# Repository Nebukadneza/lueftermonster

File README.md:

# Lüftermonster

## TL;DR:
You want to control up to 15 PC Fans by PWM, read the RPM of every single one, attach up to 4 DS18b20 Temperature Probes, and have all this exposed by API, Web-interface or into Home-Assistant? This is for you!

## Description
Many water based central heating systems that use radiators benefit from a reduced system temperature. Whether it´s fuel-value gas or oil, or a heat-pump, reducing the systems primary temperature results in energy savings.

Radiators can only radiate a certain amount of heat defined by their construction and size - unless we force some air through them! This can be done passively by building a "chimney" around them and using the chimney-effect, and/or by attaching fans. Many commercially available fan-retrofitting kits or even radiators with fans included use noisy low quality fans, don´t allow for a lot of control, and are often very expensive. So you might want to add your own.

Lüftermonster is a project that provides you with a hardware PCB and software to control up to 15 PC Fans, allowing you to make them noiseless by PWM. The tacho signals (RPM) of all fans are monitored so you can monitor them and detect broken fans. Furthermore, you can add up to 4 DS18b20 temperature sensors in order to measure water- and air-temperature to finely control your fan-speed depending on your heating and room situation. Lüftermonster is WIFI-enabled by relying on a trusty ESP32.

By implementing Lüftermonster using [ESPHome](https://esphome.io/), we make it maintainable and easily customizable. It integrates seamlessly into [Home-Assistant](https://www.home-assistant.io/) and other home-automation solutions. If you don´t have or want one, you can use the local API or web-based interface to control and monitor your Lüftermonster.

The hardware is designed so that it can be easily and affordably ordered off [JLCPCB](https://jlcpcb.com/) ready-made with components soldered by them!

# Building one
## What you need
- Lüftermonster PCB(s).
- A USB-to-Serial adapter, like the ubiquitous "FTDI" ones. Find them off your local maker store, EBay, AliExpress, Amazon or similar.
- "Dupont" female-to-female cables to connect Lüftermonster to the USB-to-Serial adapter.
- 20x5mm 2A slow fuses.
- Up to 15 PC Fans per Lüftermonster: 12V, 4-pin.
- (Optional: up to 4 DS18b20 temperature probes per Lüftermonster, including 3-pin cables)

## Hardware
### Fabrication
Gerber files and BOM/CPL data compatible with the JLCPCB assembly service can be found in the `fab` directory. This is a 2-layer PCB compatible with their "Economic" class PCBA service.

### Stuffing options

A few stuffing options are available on the PCB. The corresponding 0R resistors use 0603 sizes (compared to the 0402 size used for everything else) to be more convenient to rework with basic equipment. If you don't have KiCad installed, you can use the [Interactive HTML BOM](fab/ibom.html) to locate the components on the board.

* PWM output voltage levels. Exactly one of the following 0R resistors must be populated.
  * R10: 5V (default)
  * R11: 3.3V
  * R13: Equal to supply voltage (i.e. usually 12V)
* 1-wire supply: Exactly one of the following 0R resistors must be populated.
  * R32: 3.3V (default)
  * R12: 5V

## Software
### Preparation
Install ESPHome, please refer to their excellent ["Getting Started" Sections](https://esphome.io/). Note: You only need to get esphome itself running, not write any YAML-Files yourself.

Copy `firmware/secrets.yaml.template` to `firmware/secrets.yaml`, and edit according to your environment.

Open and edit `firmware/lueftermonster.yaml` according to your environment. Note: If you have multiple Lüftermonsters, please assign unique and meaningful names like "lueftermonster-livingroom-left" or similar.

### Programming
Connect the USB-to-Serial adapter to your Lüftermonster, as follows:
  - VCC -> 3v3
  - GND -> GND
  - RX -> TX
  - TX -> RX
  - EN -> CTS
  - IO0 -> DTR

Attach your USB-to-Serial adapter to your computer

Follow the ESPHome Getting-Started guide you´ve chosen to "run" or "upload" `firmware/lueftermonster.yaml`.

Note: `esptool`, which is internally used by ESPHome to program the ESP32 tries to reset the ESP32 and bring it into programming mode. If this does not work, it may be that "Automatic bootloader mode" does not work. Please [refer to the documentation](https://docs.espressif.com/projects/esptool/en/latest/esp32/advanced-topics/boot-mode-selection.html#automatic-bootloader).

### Usage
After a brief period, you should be able to open `http://<the-name-you-set-in-the-yaml>.local/`, for example http://lueftermonster-livingroom-left.local/ .

Now, you can control the fan speed, and check the fans current RPMs. Note: RPM are not updated often, so it make take a while for all of them to display, and for speed changes to become visible. This is intentional since the information is most useful for outage detection, and does not need to be reported often.

To connect to Home-Assistant refer to the [ESPHome documentation](https://esphome.io/guides/getting_started_hassio#connecting-your-device-to-home-assistant)

### Connect a fan
Since the "proper" PC Fan connectors are not cheaply sourcable from JLCPCB (and THT parts incur a hand-soldering fee/delay), we cheaped out by using standard 2.54mm connection pins. This works, but

_**IS NOT SAFE TO CONNECT IN REVERSE!**_

So you need to pay attention to how you connect your fans. Refer to the silk-screen on the right of Lüftermonster for the pinout of the connectors. With the two "latches" of a standard PC Fan connector, it is correct to connect the fan like this:

### Connecting DS18b20 Temperature Sensors
TODO: Section about DS18b20 address finding and such.

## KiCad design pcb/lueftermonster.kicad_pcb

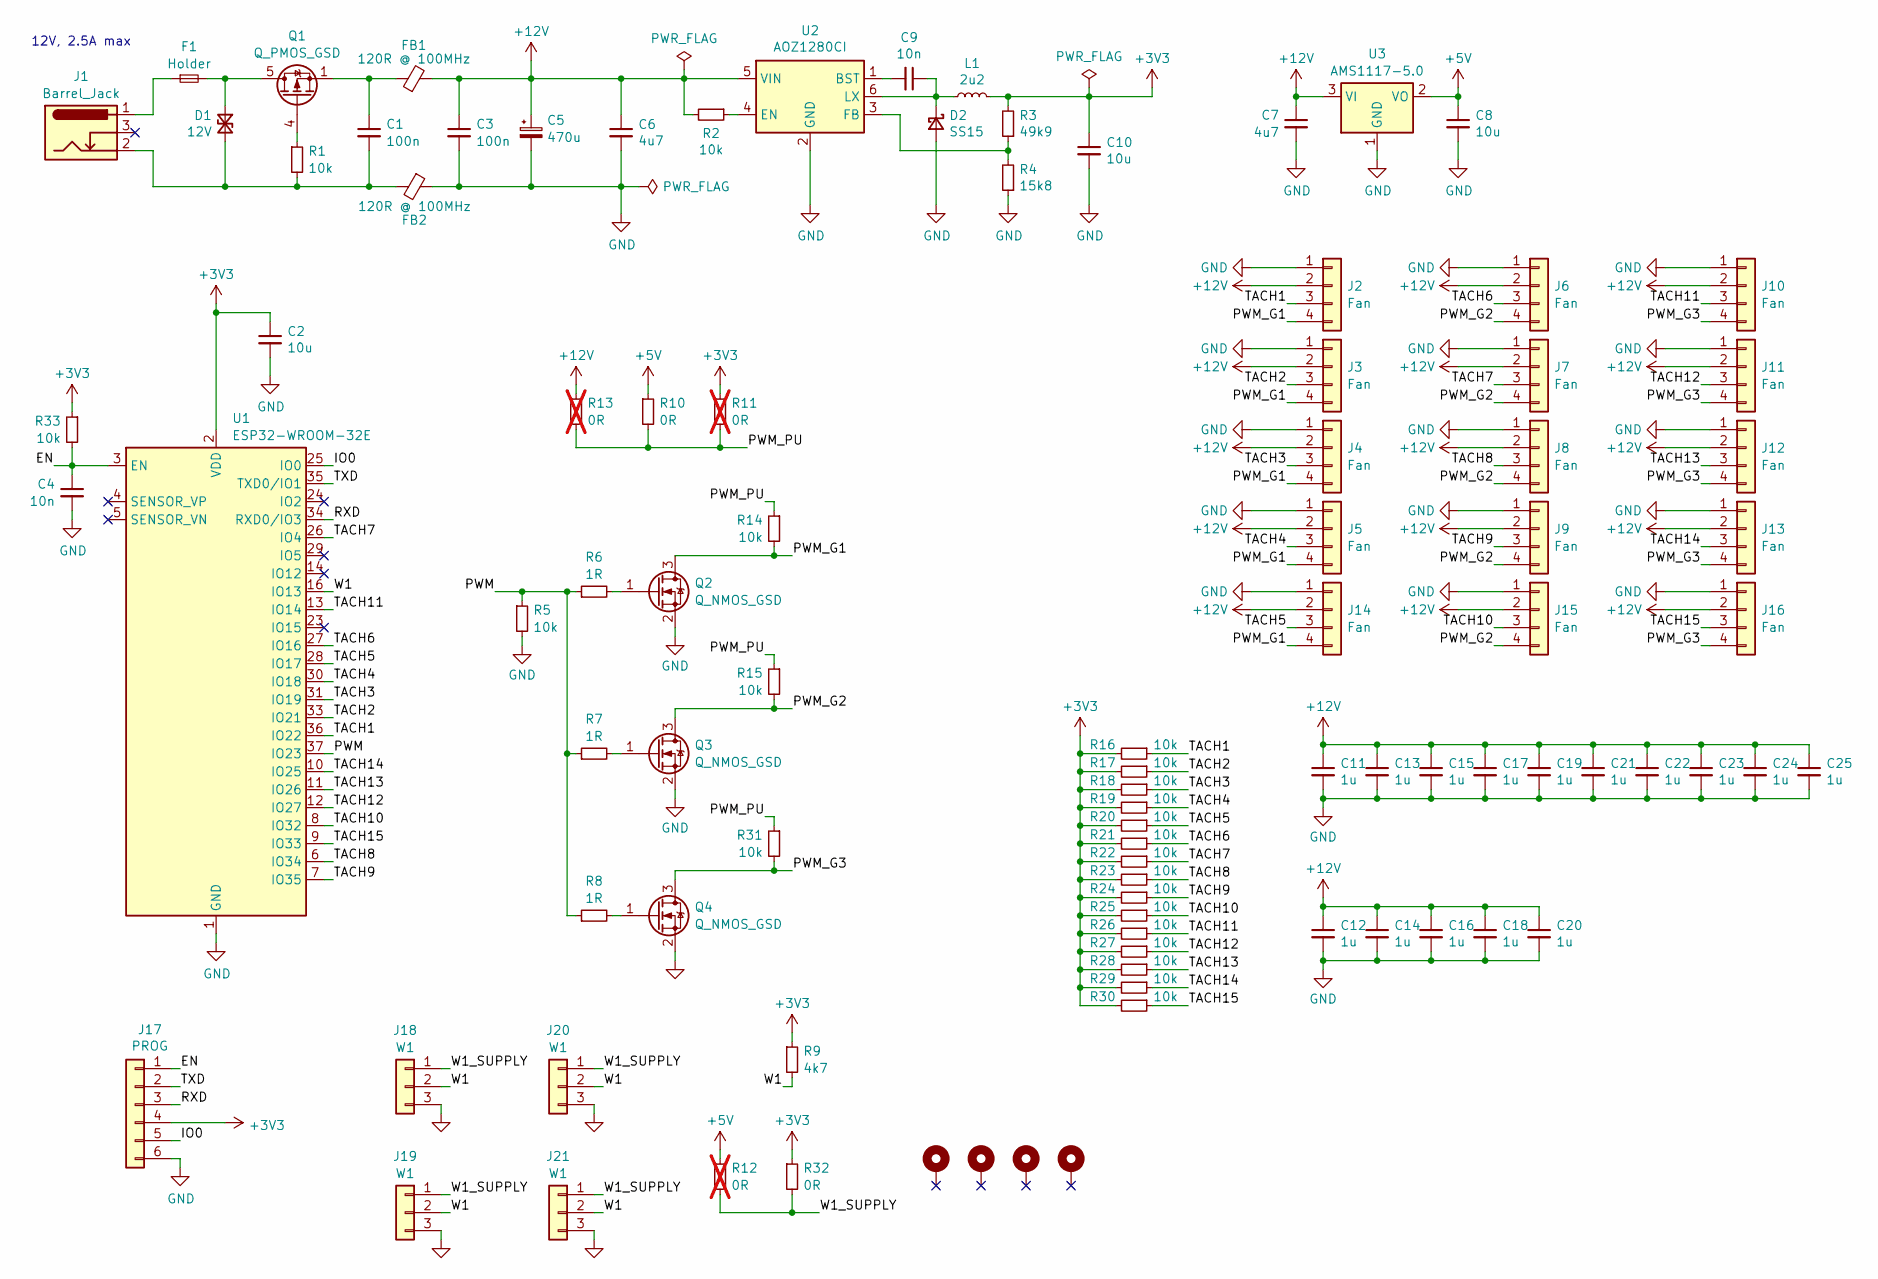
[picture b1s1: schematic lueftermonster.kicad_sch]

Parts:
C1, C3: 100n; C_0805_2012Metric; MPN CL21B104KCFNNNE; LCSC C28233
C2, C8, C10: 10u; C_0805_2012Metric; MPN GRM21BR61H106KE43L; Digikey 399-8012-1-ND
C4, C9: 10n; C_0402_1005Metric; MPN CL05B103KB5NNNC; LCSC C15195
C5: 470u; CP_Elec_10x10; MPN UWD1E471MCL1GS; LCSC C251022
C6, C7: 4u7; C_1206_3216Metric; MPN 1206B475K500NT; LCSC C29823
C11, C12, C13, C14, C15, C16, C17, C18, C19, C20, C21, C22, C23, C24, C25: 1u; C_0805_2012Metric; MPN 0805B105K500NT; LCSC C215803
D1: 12V; D_SMA; MPN SMAJ12CA; LCSC C110042
D2: SS15; D_SOD-123F; MPN B5819W SL; LCSC C8598
F1: Holder; XFCN_PTF-77; MPN PTF-77; LCSC C717030
FB1, FB2: 120R @ 100MHz; L_1206_3216Metric; MPN BLM31KN121SN1L; LCSC C337884
H1, H2, H3, H4: MountingHole_Pad; MountingHole_3.2mm_M3_ISO14580_Pad
J1: Barrel_Jack; XUNPU_DC-005-A200; MPN DC-005-A200; LCSC C720557
J2, J3, J4, J5, J6, J7, J8, J9, J10, J11, J12, J13, J14, J15, J16: Fan; PinHeader_1x04_P2.54mm_Vertical_SMD_Pin1Right; MPN X6511WVS-04H-C60D48R1; LCSC C780062
J17: PROG; PinHeader_1x06_P2.54mm_Vertical_SMD_Pin1Left; MPN X6511WVS-06H-C60D48R2; LCSC C2883763
J18, J19, J20, J21: W1; PinHeader_1x03_P2.54mm_Vertical_SMD_Pin1Left; MPN X6511WVS-03H-C60D48R2; LCSC C2883760
L1: 2u2; L_1008_2520Metric; MPN DFE252012F-2R2M=P2; LCSC C576403
Q1: Q_PMOS_GSD; Diodes_PowerDI3333-8; MPN DMP4025SFG-13; LCSC C461090
Q2, Q3, Q4: Q_NMOS_GSD; SOT-23; MPN AO3400A; LCSC C20917
R1, R2, R5, R14, R15, R16, R17, R18, R19, R20, R21, R22, R23, R24, R25, R26, R27, R28, R29, R30, R31, R33: 10k; R_0402_1005Metric; MPN 0402WGF1002TCE; LCSC C25744
R3: 49k9; R_0402_1005Metric; MPN 0402WGF4992TCE; LCSC C25897
R4: 15k8; R_0402_1005Metric; MPN 0402WGF1582TCE; LCSC C26956
R6, R7, R8: 1R; R_0402_1005Metric; MPN RTT021R00FTH; LCSC C102864
R9: 4k7; R_0402_1005Metric; MPN 0402WGF4701TCE; LCSC C25900
R10, R32: 0R; R_0603_1608Metric_Pad0.98x0.95mm_HandSolder; MPN 0603WAF0000T5E; LCSC C21189
R11, R12, R13: 0R; R_0603_1608Metric_Pad0.98x0.95mm_HandSolder; MPN 0603WAF0000T5E; LCSC C21189; not fitted
U1: ESP32-WROOM-32E; ESP32-WROOM-32D; LCSC C701342
U2: AOZ1280CI; SOT-23-6; MPN AOZ1280CI; Digikey 785-1277-1-ND
U3: AMS1117-5.0; SOT-223-3_TabPin2; MPN AMS1117-5.0; LCSC C6187

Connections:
+3V3: C2.1, C10.1, J17.4, L1.2, R3.2, R9.1, R11.1, R16.2, R17.2, R18.2, R19.2, R20.2, R21.2, R22.2, R23.2, R24.2, R25.2, R26.2, R27.2, R28.2, R29.2, R30.2, R32.1, R33.1, U1.2 (VDD)
+5V: C8.1, R10.1, R12.1, U3.2 (VO)
+12V: C3.1, C5.1, C6.1, C7.1, C11.1, C12.1, C13.1, C14.1, C15.1, C16.1, C17.1, C18.1, C19.1, C20.1, C21.1, C22.1, C23.1, C24.1, C25.1, FB1.2, J2.2, J3.2, J4.2, J5.2, J6.2, J7.2, J8.2, J9.2, J10.2, J11.2, J12.2, J13.2, J14.2, J15.2, J16.2, R2.2, R13.1, U2.5 (VIN), U3.3 (VI)
/EN: C4.1, J17.1, R33.2, U1.3 (EN)
/IO0: J17.5, U1.25 (IO0)
/PWM: R5.1, R6.1, R7.1, R8.1, U1.37 (IO23)
/PWM_G1: J2.4, J3.4, J4.4, J5.4, J14.4, Q2.3 (D), R14.2
/PWM_G2: J6.4, J7.4, J8.4, J9.4, J15.4, Q3.3 (D), R15.2
/PWM_G3: J10.4, J11.4, J12.4, J13.4, J16.4, Q4.3 (D), R31.2
/PWM_PU: R10.2, R11.2, R13.2, R14.1, R15.1, R31.1
/RXD: J17.3, U1.34 (RXD0/IO3)
/TACH1: J2.3, R16.1, U1.36 (IO22)
/TACH2: J3.3, R17.1, U1.33 (IO21)
/TACH3: J4.3, R18.1, U1.31 (IO19)
/TACH4: J5.3, R19.1, U1.30 (IO18)
/TACH5: J14.3, R20.1, U1.28 (IO17)
/TACH6: J6.3, R21.1, U1.27 (IO16)
/TACH7: J7.3, R22.1, U1.26 (IO4)
/TACH8: J8.3, R23.1, U1.6 (IO34)
/TACH9: J9.3, R24.1, U1.7 (IO35)
/TACH10: J15.3, R25.1, U1.8 (IO32)
/TACH11: J10.3, R26.1, U1.13 (IO14)
/TACH12: J11.3, R27.1, U1.12 (IO27)
/TACH13: J12.3, R28.1, U1.11 (IO26)
/TACH14: J13.3, R29.1, U1.10 (IO25)
/TACH15: J16.3, R30.1, U1.9 (IO33)
/TXD: J17.2, U1.35 (TXD0/IO1)
/W1: J18.2, J19.2, J20.2, J21.2, R9.2, U1.16 (IO13)
/W1_SUPPLY: J18.1, J19.1, J20.1, J21.1, R12.2, R32.2
GND: C2.2, C3.2, C4.2, C5.2, C6.2, C7.2, C8.2, C10.2, C11.2, C12.2, C13.2, C14.2, C15.2, C16.2, C17.2, C18.2, C19.2, C20.2, C21.2, C22.2, C23.2, C24.2, C25.2, D2.2 (A), FB2.1, J2.1, J3.1, J4.1, J5.1, J6.1, J7.1, J8.1, J9.1, J10.1, J11.1, J12.1, J13.1, J14.1, J15.1, J16.1, J17.6, J18.3, J19.3, J20.3, J21.3, Q2.2 (S), Q3.2 (S), Q4.2 (S), R4.1, R5.2, U1.1 (GND), U1.15 (GND), U1.38 (GND), U1.39 (GND), U2.2 (GND), U3.1 (GND)
unnamed: C1.1, FB1.1, Q1.1 (S), Q1.2 (S), Q1.3 (S)
unnamed: D1.1 (A1), F1.2, Q1.5 (D)
unnamed: C1.2, D1.2 (A2), FB2.2, J1.2, R1.2
unnamed: C9.1, D2.1 (K), L1.1, U2.6 (LX)
unnamed: F1.1, J1.1
unnamed: Q1.4 (G), R1.1
unnamed: Q2.1 (G), R6.2
unnamed: Q3.1 (G), R7.2
unnamed: Q4.1 (G), R8.2
unnamed: C9.2, U2.1 (BST)
unnamed: R2.1, U2.4 (EN)
unnamed: R3.1, R4.2, U2.3 (FB)

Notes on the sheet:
12V, 2.5A max

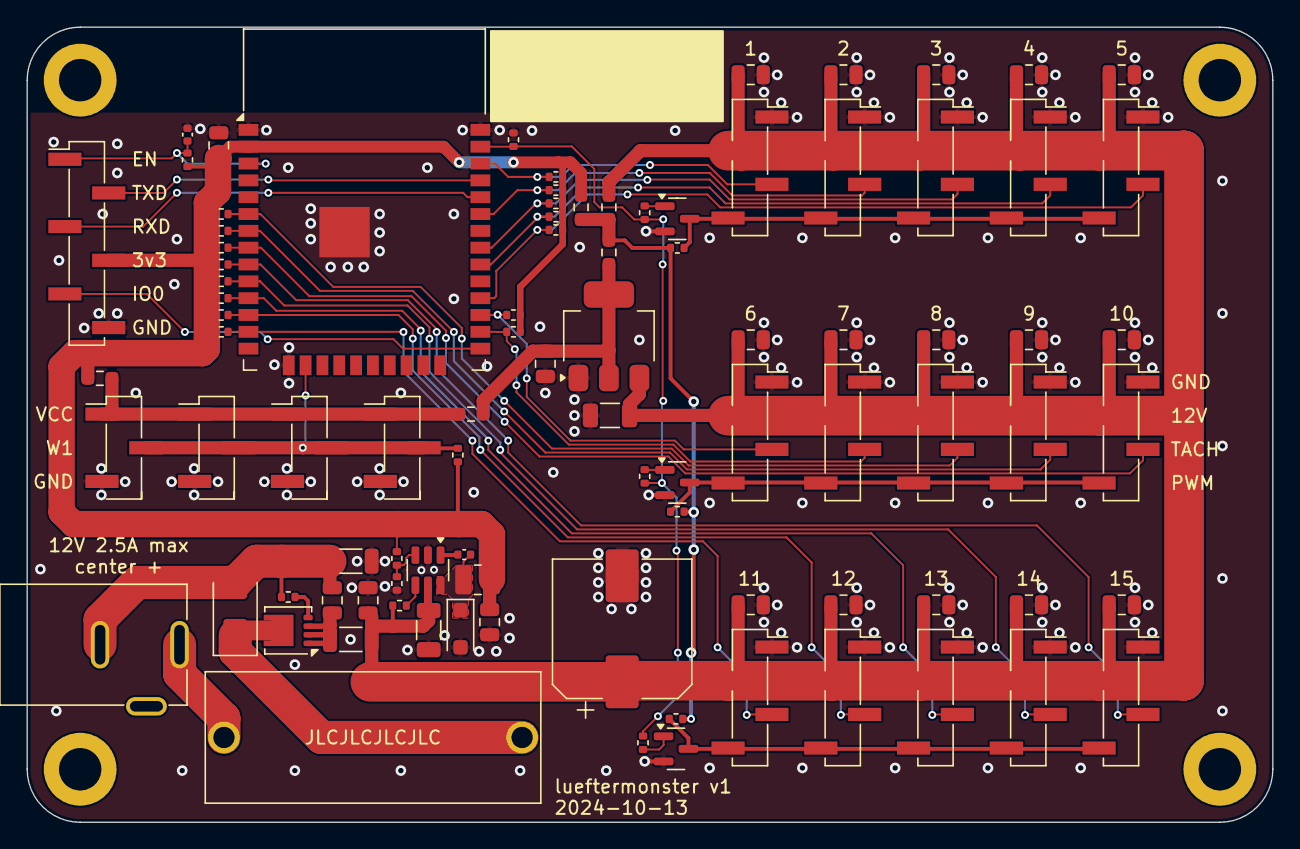
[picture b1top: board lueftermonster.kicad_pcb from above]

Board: 2 copper layers, 94.0 x 60.0 mm, 96 parts (0 on the bottom side), 42 nets.

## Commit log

2024-06-05 import
2024-06-05 more bom
2024-06-05 unfuck fields
2024-06-05 unfuck fields even harder
2024-06-05 more bom, all the heavy hitters are in now
2024-06-05 bullshit placing to make gerbers sane
2024-06-05 snap
2024-10-12 use 100mil headers for fans
2024-10-12 finalize bom, add LED
2024-10-12 0 nets
2024-10-13 DRC clean
2024-10-13 stitch
2024-10-13 update bom
2024-10-13 tweaks
2024-10-13 replace out of stock 1R 0402
2024-11-11 Add initial firmware as esphome yaml
2024-11-11 Move wifi credentials to secrets
2024-11-11 Add comments for clarity
2024-11-11 Add first readme
2024-11-11 Add photo to readme
2024-11-11 Add fan connection section to readme
2024-11-12 add fab data
2024-11-12 add ibom, update readme
2024-11-12 Move PCB Design files to subdir
